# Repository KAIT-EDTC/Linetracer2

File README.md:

# Linetracer2 — 子ども向け教材ライントレーサー

Raspberry Pi Pico ＋ TC78H653FTG ＋ 130 モーター ×2 の、**全部足付き部品（スルーホール）で子どもが自分ではんだ付けできる**ライントレーサー。
基板そのものがシャーシで、センサー 6 個を基板の裏に直付けし、3D プリント（Bambu Lab P1S）のギヤボックス（1 段 5:1）で 130 モーターを高速に回す。
**テープ・接着剤は使わず、M3 ねじ（2 種類）と 3D プリントのツメで組み立てる。** 部品は秋月・ホームセンター・タミヤ品など、**T 番号のある店で買える定番品だけ**。

| 基板（表） | 組み立て図 |
|---|---|
|  |  |

| 項目 | 内容 |
|------|------|
| マイコン | Raspberry Pi Pico（Pico 2 / Pico W も可）、MicroPython |
| モータードライバ | 東芝 TC78H653FTG（秋月 AE-TC78H653FTG モジュール ¥200、スモールモード 2A×2ch） |
| モーター・駆動 | FA-130RA-2270 ×2、タミヤ 8T ピニオン → 3D プリント 40T（m0.5）1 段 5:1、車輪 φ32（O リング P-24）、車軸は車輪と一体で印刷（φ3.5） |
| センサー | フォトリフレクタ LBR-123F ×6（TC4051BP で ADC 1 本に切替、外乱光キャンセル付き） |
| 電源 | 単3×3本（アルカリ 4.5V / ニッケル水素 3.6V）。電池ボックスはデッキにねじ止め、スイッチで ON/OFF |
| 基板 | 2 層 100×100 mm、1.6 mm、全部品スルーホール（ピッチ 2.54 mm 以上、センサーのみ 1.8 mm）、**rev.A1** |
| 3D プリント | 枠 L/R・デッキ・平歯車 ×2・車輪 ×2・ツメで差し込むスキッド（PLA 約 30 g、サポート不要）。電池ボックスをツメで留めるデッキも用意（任意） |
| UI | ボタン×2（START/SELECT）、LED×3、圧電ブザー（オプション）、I2C 拡張（OLED を直挿し可） |
| 性能（計算値） | 最高速度 理論 5 m/s（ソフトで 1.5〜2.5 m/s に制限）、加速 4 m/s² でモーター電流 約 1.4 A |
| コスト（1 台） | 全部新品 約 ¥2,370、**Pico を再利用すれば 約 ¥1,500**（`docs/05_bom.md`） |

## 「Linetracer2 Lite」（rev.L4：XIAO ESP32C6（ピンヘッダ）＋ LBR-127HLD ＋ ブザー ＋ フルカラー LED ＋ 5 V 昇降圧）

標準版から部品を減らした版も用意した（詳しくは [lite/README.md](lite/README.md)）。**Lite のファイルはすべて `lite/` フォルダにまとめてあり、標準版のファイルとは混ざらない**。**枠・デッキ・平歯車・車輪の 3D プリント部品、ねじ、モーター、電池ボックスは標準版と共通**で、基板・ソフト・前の支え（Lite 用ボールキャスター）が違う。
rev.L2（2026-10-05）でマイコンを **Seeed Studio XIAO ESP32C6**、センサーを **LBR-127HLD** に変え、rev.L3（2026-10-07）で **XIAO をピンヘッダ付けに、ブザーとフルカラー LED 6 こ・テストパッドを追加、配線を全部手で引き直し（交差なし・ビア 0）、Lite 用ボールキャスター**を作った。ロボット全体の 3D モデル（STL / GLB）もある。
**rev.L4（2026-10-30）**: モーターに力がかかる（車輪を止める・100 % で走り出す）と電池が 2.5〜3.3 V まで下がって XIAO がリセットしていたので、**XIAO の電源を昇降圧モジュール（秋月 AE-TPS63802、5 V）で作る**ようにし、ほかの回路の問題（USB の VBUS に 470 µF、フルカラー LED の信号の電圧、ニッケル水素で動かない など）も直した（[lite/README.md](lite/README.md) §0）。**KiCad のファイル・Gerber はまだ rev.L3 のまま**（生成スクリプトは rev.L4。KiCad 10 で作り直してから発注）。

| | 標準版 rev.A1 | Lite rev.L4 |
|---|---|---|
| マイコン | Pico をピンヘッダで付ける | **XIAO ESP32C6 をピンヘッダで付ける**（Wi-Fi / Bluetooth 付き） |
| センサー | LBR-123F 6 個 ＋ マルチプレクサ TC4051BP | **LBR-127HLD 3 個を ADC に直結**（マルチプレクサなし） |
| ボタン / LED / ブザー | 2 / 3 / オプション | **1 / フルカラー 6（PL9823、左右に 3 こずつ、信号線 1 本）/ あり（START ボタンと同じピン）**（XIAO の黄 LED も使える） |
| タイヤ / 前の支え | O リング P-24 / スキッド 4.0 mm | **TPU の印刷タイヤ / ボールキャスター 7.5 mm**（センサーが背高なので前を上げる） |
| マイコンの電源 | 電池 → ダイオード → Pico の VSYS（Pico の中は昇降圧） | **電池 → 昇降圧モジュール AE-TPS63802（5 V）→ ダイオード → XIAO の 5V ピン**（rev.L4。モーターで電池が下がっても XIAO が止まらない） |
| 電池電圧の測定 | あり | **なし**（XIAO の ADC 3 本をセンサーで使い切る） |
| はんだ付け | 約 230 か所 | **約 146 か所** |
| 基板 / シルク | 100 × 100 mm / 英語中心 | **65 × 100 mm** / **記号だけ**（つくる順番 ①〜⑰・＋−・抵抗の色）。説明は手順書 `lite/docs/assembly.md` |
| **1 台の部品代（全部新品）** | 約 ¥2,370 | **約 ¥3,530（+¥1,160。うち 5 V 昇降圧モジュール ¥780）** |

> Lite rev.L3 / L4 はマイコンをピンヘッダで付ける。基板側を**ピンソケット**にすれば、標準版のようにマイコンを回収して使い回すこともできる（`lite/docs/assembly.md` §3）。

| Lite のロボット全体（3D） | Lite の基板（3D） |
|---|---|
|  |  |

## ドキュメント

| ファイル | 内容 |
|---------|------|
| [docs/01_requirements.md](docs/01_requirements.md) | 要件定義（依頼内容・派生要件・買い方のルール・コスト目標） |
| [docs/02_concept.md](docs/02_concept.md) | 形・寸法・駆動系の計算・重心・電池 |
| [docs/03_circuit.md](docs/03_circuit.md) | 回路設計（ピン割り当て表、各ブロックの計算） |
| [docs/04_pcb.md](docs/04_pcb.md) | 基板設計（改訂履歴・配置・配線・DRC・発注方法・再生成方法） |
| [docs/05_bom.md](docs/05_bom.md) | 部品表（秋月の通販コード・買う店）、コスト、10 台分の買い物リスト |
| [docs/06_assembly.md](docs/06_assembly.md) | 組み立て手順書（はんだ付けの順番・チェック・ねじ止め・トラブル） |
| [docs/07_firmware.md](docs/07_firmware.md) | ソフトウェア（MicroPython のセットアップ、ライブラリ、PD 制御の調整） |
| [docs/08_knowledge.md](docs/08_knowledge.md) | 知見メモ（部品のクセ、買い方、KiCad/Freerouting/OpenSCAD のハマりどころ、設計判断） |
| [lite/README.md](lite/README.md) | **Lite rev.L4**（**§0: XIAO が落ちる原因と電源の作り直し**、XIAO ESP32C6 ＋ LBR-127HLD ＋ ブザー。変更点と理由、配線のルール、コスト比較、回路・基板・部品表・組み立て・ソフトの違い） |
| [lite/docs/assembly.md](lite/docs/assembly.md) | Lite の組み立て手順書（基板の記号の見かた、つくる順番 ①〜⑰） |
| [lite/hardware/Linetracer2-Lite_assembly.stl](lite/hardware/Linetracer2-Lite_assembly.stl) | **Lite のロボット全体の 3D**（基板・部品・枠・モーター・ギヤ・電池ボックス・キャスター。STL、ブラウザで回して見られる。色つきは同じ名前の `.glb`） |
| [hardware/mechanical/README.md](hardware/mechanical/README.md) | 3D プリント部品と P1S の印刷設定、ねじの一覧 |
| [hardware/mechanical/assembly.stl](hardware/mechanical/assembly.stl) | 全体を組み立てた 3D（STL、ブラウザで回して見られる） |
| [hardware/kicad/Linetracer2_pcb.step](hardware/kicad/Linetracer2_pcb.step) | 部品付き基板の 3D（STEP、Fusion 等の CAD 用） |
| [docs/Linetracer2_schematic.pdf](docs/Linetracer2_schematic.pdf) | 回路図 PDF |
| [lite/docs/Linetracer2-Lite_schematic.pdf](lite/docs/Linetracer2-Lite_schematic.pdf) | Lite の回路図 PDF |
| [docs/datasheets/README.md](docs/datasheets/README.md) | 使った部品のデータシート（リンク集） |

## フォルダ構成

```
Linetracer2/
├── README.md
├── docs/                     設計資料（Markdown）、回路図/基板 PDF、画像、データシートのリンク
├── hardware/
│   ├── kicad/                KiCad 10 プロジェクト（.kicad_pro / _sch / _pcb）
│   │   ├── lib/              自作シンボル・フットプリント（TC78H653 モジュール、LBR-123F、ブザー等）
│   │   ├── bom/              部品表 CSV（秋月の通販コード入り）
│   │   └── reports/          ERC / DRC レポート、ネットリスト
│   ├── gerber/               製造用 Gerber・ドリル
│   ├── Linetracer2_rev.A1_gerber.zip   ← 基板メーカーにそのまま渡す
│   └── mechanical/           3D プリント部品（OpenSCAD 元データ、STL、組み立て図。両方の版で共通。Lite は前の支えだけ 7.5 mm）
├── firmware/micropython/     ライブラリ・標準プログラム・授業用サンプル
├── scripts/                  回路図・基板を生成するスクリプト（再生成用。LT2_VARIANT=lite で Lite も作る）
└── lite/                     ★ Lite 一式（rev.L4: XIAO ESP32C6 版。標準版とは別フォルダ）
    ├── README.md             Lite の設計書（変更点・コスト比較・組み立て・ソフト）
    ├── docs/                 回路図/組立図 PDF、3D 画像
    ├── hardware/             KiCad プロジェクト、Gerber（Linetracer2-Lite_rev.L3_gerber.zip）、ロボット全体の 3D（STL / GLB）
    ├── firmware/micropython/ Lite 用ソフト（XIAO ESP32C6 用 MicroPython。センサー 3 個・ボタン 1 個・フルカラー LED 6 個・ブザー）
    └── scripts/              Lite 専用の生成スクリプト（回路図・配置と手で引いた配線・シルク・配置の確認用の絵）
```

## 状態（2026-10-05, rev.A1）

- [x] 要件定義・構成・駆動系の計算
- [x] 回路図（ERC エラー 0・警告 0）
- [x] 基板レイアウト・配線（DRC エラー 0、未配線 0）、Gerber 出力（rev.A1: ブザーの穴を追加）
- [x] 部品選定・BOM・コスト見積り（T 番号のある店・定番品だけ）
- [x] 3D プリント部品（ねじ止めのデッキ、印刷できる 40T 平歯車、干渉チェック済み）
- [x] MicroPython ライブラリとサンプル
- [ ] **試作 1 台目の製作と実測**（センサーの感度、ギヤのかみ合い、PD ゲイン、電池の持ち）
- [ ] 試作結果を反映した rev.B（`docs/04_pcb.md` §7）
- [x] 低コスト版 Lite rev.L1 の回路図・基板（ERC 0・DRC 0・警告 0）・部品表・ソフト（2026-10-05）
- [x] Lite rev.L2（XIAO ESP32C6 ＋ LBR-127HLD）の回路図・基板・部品表・ソフト・スキッド 7.5 mm（2026-10-05）
- [x] Lite rev.L3（XIAO をピンヘッダで、ブザー、手で引いた配線、Lite 用ボールキャスター、ロボット全体の 3D と干渉チェック）（2026-10-07）
- [x] Lite rev.L4 の回路・配置と配線（生成スクリプト）: XIAO 用 5 V 昇降圧、USB と電源の分け方、フルカラー LED の信号の電圧（2026-10-30）
- [ ] Lite rev.L4 を KiCad 10 で作り直す（回路図・基板・DRC・Gerber・絵・3D、`lite/README.md` §0.6・§9）
- [ ] Lite の試作（LBR-127HLD の高さ、キャスターの転がり、3 センサーでの走り、`lite/README.md` §10）

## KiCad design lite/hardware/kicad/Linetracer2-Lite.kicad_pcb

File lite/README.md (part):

# Linetracer2 Lite（rev.L4：XIAO ESP32C6（ピンヘッダ）＋ LBR-127HLD ＋ ブザー ＋ フルカラー LED ＋ 5 V 昇降圧）

> 最終更新: 2026-10-30（**rev.L4**: モーターに力がかかると XIAO が落ちる問題を、マイコンの電源を作り直して直した（§0）。**未製造・未試作**）
> **注意: KiCad のファイル（回路図・基板・Gerber・PDF・絵・3D）はまだ rev.L3 のまま**。rev.L4 は生成スクリプトに入っている。§9 のコマンドで作り直し、DRC を通してから発注する。**今の Gerber（rev.L3）は発注しない**（§0.6）。
> 標準版（rev.A1）から部品を減らした版。マイコンは **Seeed Studio XIAO ESP32C6**、センサーは **LBR-127HLD**。rev.L3 で **XIAO をピンヘッダで付ける**ようにし、**ブザー**と**フルカラー LED 6 こ**、**テストパッド**を足し、**配線を全部手で引き直して**（自動配線をやめた）、**Lite 用のボールキャスター**を作った（§1）。
> **枠・デッキ・平歯車・車輪の 3D プリント部品、ねじ、モーター、電池ボックス、枠のねじ穴は標準版と共通**。違うのは基板（外形と中身）・ソフト・**前の支え（高さ 7.5 mm のボールキャスターかスキッド）**。
> **Lite のファイルはすべてこの `lite/` フォルダの中**（下のパスは `lite/` からの相対パス）。標準版のファイル（リポジトリ直下の `hardware/` `docs/` `firmware/`）とは混ざらない。
> 回路図: `hardware/kicad/Linetracer2-Lite.kicad_sch`（PDF: `docs/Linetracer2-Lite_schematic.pdf`）
> 製造データ: `hardware/Linetracer2-Lite_rev.L3_gerber.zip`（**rev.L3、XIAO が落ちる問題あり**。rev.L4 は KiCad で作り直すと `Linetracer2-Lite_rev.L4_gerber.zip`）　ソフト: `firmware/micropython/`（Arduino C++ 版: [`firmware/arduino/`](firmware/arduino/README.md)）　組み立て手順書: [`docs/assembly.md`](docs/assembly.md)
> **ロボット全体の 3D モデル**: `hardware/Linetracer2-Lite_assembly.stl`（GitHub 上でそのまま回して見られる）、色つき `hardware/Linetracer2-Lite_assembly.glb`。部品付き基板だけの STEP: `hardware/kicad/Linetracer2-Lite_pcb.step`
> 前の版 rev.L2（XIAO じか付け、自動配線）は git の履歴とプルリクエスト #3 に、rev.L1（Pico ＋ LBR-123F）はコミット `1db5a53` に残っている。

| ロボット全体（3D） | 横から |
|---|---|
|  |  |

| 基板の上面（3D） | 裏面（3D、センサー面） |
|---|---|
|  |  |

| シルク（表。子どもが読む印刷） | シルク（裏、下から見た向き） |
|---|---|
|  |  |

---

## 0. rev.L4（2026-10-30）: モーターに力がかかると XIAO が落ちる → 電源を作り直した

依頼「モーターにトルクをかけたときや、モーター出力 100 % にしたときに XIAO が落ちるので回路を組み直して。ほかにも回路的に良くないところ・問題点をくまなく見て」への答え。

### 0.1 原因: XIAO の電源が、モーターと同じ電池から「ダイオード 1 本」でとっていた

rev.L3 は `単3×3 ─ D1 ─ XIAO の 5V ピン` だった。XIAO の中は `5V ピン ─ ショットキー（約 0.3 V）─ 降圧 DC-DC ─ 3.3 V` なので、3.3 V を保つには電池の側で**約 4.0 V**、ESP32-C6 がリセットしないためにも**約 3.4 V** 要る。ところが単3 アルカリ 3 本は、モーターが大きい電流を流すとすぐその下まで下がる。

計算の前提: 電池 3 本 ＋ 電池ボックスのばね・スイッチ・線の抵抗 ≒ 0.7 Ω（新品）、FA-130RA-2270 の巻線 ≒ 0.68 Ω（1.5 V で止めると 2.2 A）、TC78H653FTG（スモールモード）のオン抵抗 0.22 Ω、ソフトの 100 % = 電池の 71 %（3.0 V ÷ 4.2 V）。

| 場面 | 電池から出る電流 | 電池の電圧（新品 4.65 V） | rev.L3 の XIAO |
|---|---|---|---|
| ふつうに走っている（2 つで 1 A くらい） | 約 1.0 A | 約 3.9 V | ぎりぎり動く |
| **片方の車輪を手で止めて 100 %**（もう片方は止まっている） | 約 1.9 A | **約 3.3 V** | **リセット** |
| **2 つとも 100 % で走り出す・2 つとも止める** | 約 2.9 A | **約 2.6 V** | **リセット** |
| （少し減った電池 3.9 V・1.2 Ω で 2 つとも止める） | 約 1.9 A | 約 1.7 V | リセット |

- 470 µF（C2）は 0.2 A で 1 ms ほどしか持たない。モーターが止まっている間（何百 ms）は支えられない。
- つまり**ソフトの問題ではなく、電源の作り方の問題**。走り出しのソフトスタート（`RAMP_PER_CALL`）は入っているが、車輪を止められると電流は減らない。
- 標準版（Pico）では起きにくい: Pico の VSYS の中に**昇降圧の DC-DC（1.8〜5.5 V）**があるから。XIAO ESP32C6 の中は降圧だけなので、Lite では外に昇降圧が要る。

### 0.2 なおしかた: XIAO 専用の 5 V を、昇降圧モジュールで作る

```
単3×3 ─ VBAT ─┬─ モータードライバ VM（C1 470µF）
              └─ D1 1N5819 ─ VIN_BB ─ U3 AE-TPS63802（昇降圧、VR1 = 470kΩ → 5.13 V、EN = VIN）
                                        └─ VOUT_BB ─ D8 1N5819 ─ VSYS（約 4.8 V）─┬─ XIAO 5V ピン → 3.3 V
                                                                                   ├─ 右のフルカラー LED 3 こ（D5〜D7）
                                                                                   └─ D9 1N4148 ─ VLED_L（約 4.1 V）─ 左の 3 こ（D2〜D4）
              USB-C の 5 V も VSYS に来る（XIAO の中で直結）。D8 があるので U3 には流れない
```

- **U3 = 秋月 AE-TPS63802**（TI TPS63802 の昇降圧モジュールキット、¥780、20 × 13 mm、4 ピン: VIN・GND・VOUT・EN）。**入力 1.3〜5.5 V で動き続け**（はじめの起動は 1.8 V 以上）、スイッチ電流 2 A。電池が**約 1.6 V**（D1 のあとで 1.3 V）まで下がっても XIAO に 5 V を出す。上の表のいちばん悪い場面（2.6 V）でも余裕がある。
  - 昇圧だけでなく**昇降圧**なので、新品のアルカリ（4.8 V）でもニッケル水素（3.6 V）でも同じ 5.13 V。
  - 秋月で買えて、ピンヘッダで付けられて、1 A 近く出せるのはこれだけだった。もっと安い昇圧モジュール（AE-XCL102 / XCL103、5 V）は出力 0.2 A ほどで、Wi-Fi（`03_WiFiControl`）やフルカラー LED を使うと足りない。
  - 出力は VR1（25 回転の半固定抵抗）で決まる。**VR1 の代わりに 470 kΩ の抵抗を付けて 5.13 V に固定**（秋月の説明書の表の値。半固定抵抗だと回してしまう・高さがある）。**VR1 が空のまま電気を入れるとこわれる**ので、先生が先に付けて単3 ×2 本でためす（手順書 §0）。
  - EN は VIN につないで「いつも ON」（TI の注意: EN を浮かせてはいけない）。モードのジャンパーはそのまま（強制 PWM）。
- **D8**（1N5819）: XIAO の 5V ピンは USB の VBUS と直結。D8 が無いと、U3 が PC の USB に電気を押しこみ、USB の 5 V が U3 の出力に逆から入る。D8 のおかげで VSYS は約 4.8 V（USB の 5 V より少し低い）: **USB をつなぐと USB から、外すとすぐ U3 から**。
- **D1**（1N5819）はそのまま: 電池を逆につないだとき、U3 と XIAO を守る（U3 の入力は −0.3 V まで）。
- **C2（VSYS の 470 µF）はやめた**: VSYS は USB の VBUS そのもので、USB の決まりは 10 µF まで（差した瞬間の突入電流で PC のポートが落ちることがある）。U3 の出力にはモジュールのコンデンサがある。
- XIAO の 5V ピンには約 4.8 V。中の降圧 DC-DC にとって十分（3.6 V 以上あればよい）。

### 0.3 ほかに見つけた回路の問題と対応

| # | 問題 | どうなるか | rev.L4 |
|---|---|---|---|
| 1 | **XIAO の電源が電池じか**（§0.1） | モーターに力がかかると XIAO がリセット | **U3（5 V 昇降圧）を足した** |
| 2 | **ニッケル水素 3 本（3.6 V）だと、止まっていても足りない**（rev.L3 の説明は「NiMH は `BATTERY_VOLT` を 3.7 に」としていたが、XIAO の 3.3 V が保てない） | 不安定・動かない | U3 で解決（NiMH でも 5.13 V。内部抵抗が小さいのでモーターにはむしろよい） |
| 3 | **USB の VBUS（= VSYS）に 470 µF（C2）** | USB を差した瞬間の突入電流（規格は 10 µF まで）。PC のポートが落ちる・つながらないことがある | C2 をやめた（部品が 1 つ減った） |
| 4 | **フルカラー LED の信号の電圧が足りない**: PL9823 は VDD の 0.7 倍より高いと「1」。USB の 5 V では 3.5 V 要るが、XIAO は 3.3 V | USB だけだと光らない・色がおかしい（rev.L3 §10 で心配していたこと）。U3 で VSYS が 4.8 V に上がると電池でも同じになる | **左の 3 こ（信号が最初に入る D2 を含む）の電源を D9（1N4148）で 0.7 V 下げた**: 約 4.1 V → 2.9 V で「1」。D2〜D4 は自分の VDD（4.1 V）で次へ信号を渡すので、右の 3 こ（4.8 V → 3.4 V）にも足りる |
| 5 | フルカラー LED の電源が電池 − D1（新品で約 4.2 V）で、決まり（4.5〜6 V）より低い | 電池が減ると青と緑が暗くなる | 右の 3 こは 4.8 V（決まりの中）。左の 3 こは 4.1 V（rev.L3 と同じくらい、でも電池が減っても変わらない） |
| 6 | 電池の電圧を測れない（ADC のピンが 3 本しかなく、センサーで使っている） | 電池が減ったのが分からない | 変わらず。rev.L4 ではリセットしなくなる代わりに、だんだん遅くなる。ほぼ空（約 1.6 V）で U3 が止まる → XIAO がリセット（「ド・ミ・ソ」がまた鳴る）が電池交換のサイン |
| 7 | 電池の ＋ − が逆（J1 を逆にはんだ付けしたとき） | モータードライバの中のダイオードで電池がショートする（ドライバがこわれ、電池・線が熱くなる） | 変わらず（D1 が U3 と XIAO は守る）。ショート対策のリセッタブルヒューズ（PTC）は、0.1 Ω ほどの抵抗でモーターの電圧をさらに下げ、モーターを止めたときの電流で切れてしまうので見送り。手順書 ⑩ ★ の向きの確認で防ぐ |
| 8 | 車輪を止めたまま 100 % を続けると、ドライバの過電流保護（ISD）が働き、ソフトが 0.1 秒ごとに戻す | 大きい電流がくり返し流れ、モーターが熱くなる | rev.L3 では XIAO がリセットして（たまたま）止まっていた。rev.L4 では止まらないので、**車輪を手で止めつづけない**（電流を測るピンがないのでソフトでは見分けられない） |
| 9 | フルカラー LED にパスコン（0.1 µF）がない | ちらつくかもしれない | 変わらず。VSYS は U3 の出力で安定するようになった。ちらつくなら次の版で足す（§10） |
| 10 | XIAO の 5V ピンは USB と直結 → 外の電源は必ずダイオード経由 | ― | rev.L3（D1）と同じ考えで D8 |

ソフトの変更はない（ピンは rev.L3 と同じ）。`linetracer.py`・Arduino 版のコメントと、`08_test_pads.py` の VSYS の目安だけ直した。

### 0.4 配置と配線（rev.L4）

（`scripts/preview_layout.py` の絵。赤 = 表、青 = 裏。KiCad で作った絵ではない）

- **U3 は真ん中**（ブザーと XIAO のアンテナの間）に、自分のピンヘッダでねかせる（2.5 mm 浮く）。下は線だけ（3 本のバスなど）。XIAO のアンテナの禁止エリアから 2 mm、IN2 の線から 0.4 mm。
- **D1・D8 は U3 の左にたてに 2 本**。D9 は前の R7 と R1 の間（裏の横の線（VSYS）を D9 で 2 つに分けた）。
- **電池（U3 の入力）と 5 V（VSYS）は、モータードライバのモジュールの下**（2 列のピンの間。モジュールは 2.5 mm 浮いている）を 2 本の線で通した。右うしろ（ドライバの VM のピン、XIAO の 5V ピン）から真ん中へ、XIAO のアンテナの禁止エリアと STBY の線（裏）をよけて、**交差なしで行ける道はここだけ**。線の太さは 0.6 mm（1 A まで）、ビア 0 のまま。
- C2・前の D1 の場所（右うしろ）があいたので、ロボットの名前をそこへ。テストパッド GND（TP1）はスタートボタンのうしろへ（前の場所は U3 の下になる）。**抵抗の絵は U3 の四角の中**（抵抗は ①〜③、U3 は ⑬ なので、使うときには見える）。
- つくる順番を **①〜⑰** に付け直した: ④ 1N5819 ×2（D1・D8）→ ⑤ 1N4148（D9）→ ⑥ 0.1 µF → ⑦ トランジスタ → ⑧ ボタン → ⑨ ブザー → ⑩ でんち → ⑪ ドライバー → ⑫ XIAO → **⑬ でんげん（U3）** → ⑭ フルカラー LED → ⑮ 470 µF（C1 だけ）→ ⑯ センサー（裏）→ ⑰ モーター。
- 確かめたこと: 線は縦・横・45° だけ（`check_angles()`）。KiCad の DRC の代わりに、配置・配線のデータから**すき間 0.2 mm 以上と、全部のネットがつながっていること**を調べる簡単なチェックを作って、**エラー 0**（同じチェックで rev.L3 も 0、わざと近づけると検出する）。**KiCad の DRC・回路図との照合はまだ**（§0.6）。
- **U3 の外形は推定**: 秋月の資料の寸法（20 / 13 / 1.8 / 2.7 / 2.54 mm）から「4 本のピンが 13 mm の辺に、端から 1.8 mm」とした。モジュールは**裏返してもピンは同じ穴のまま、体が列の反対側に来る**ので、四角に入る向きで付けられる（部品の面を下にするときは VR1 の 470 kΩ をねかせて 2.5 mm 以下）。**発注の前に実物か秋月の外形図で確かめる**（§10）。

### 0.5 部品とコスト（1 台）

| | 変化 |
|---|---|
| U3 昇降圧モジュール AE-TPS63802（秋月 115557、4 ピンのピンヘッダ付き） | +¥780 |
| VR1 の代わりの抵抗 470 kΩ（125474） | +¥1 |
| D8 1N5819（D1 と同じ） | +¥10 |
| D9 1N4148 | +≒¥2 |
| C2 470 µF をやめた | −¥10 |
| **合計** | **+≒¥783 → 1 台 約 ¥3,530**（rev.L3 約 ¥2,745） |

はんだ付けは子どもが +6 か所（U3 の 4、D8・D9、C2 −2）、先生が U3 の準備で 6 か所（ピンヘッダ 4、470 kΩ 2）。

### 0.6 このとき作ったもの・まだのもの

| | 状態 |
|---|---|
| 回路図の生成 `scripts/gen_schematic_lite.py` | **rev.L4**（このスクリプトの出力を読む簡単なネットリスタで、ネットが意図どおりか確かめた） |
| シンボル・フットプリント・3D `../scripts/gen_lib.py`・`gen_3d.py` | **rev.L4**（`AE-TPS63802` を追加） |
| 配置と配線 `scripts/layout_lite.py`、シルク `scripts/post_pcb_lite.py`、手順の絵 `scripts/step_images.py` | **rev.L4** |
| ソフト（MicroPython / Arduino） | コメントと目安だけ（ピンは同じ） |
| この README、手順書 `docs/assembly.md`、部品表 `docs/bom.md` | **rev.L4** |
| `hardware/kicad/*.kicad_sch` / `*.kicad_pcb` / ライブラリ、Gerber、BOM の csv、PDF、`docs/*.png`、STEP、ロボット全体の 3D、手順の絵 `docs/steps/` | **まだ rev.L3**。このセッションでは KiCad 10 を入れられなかった（配布元につながらず、ソースからのビルドは止められた）。§9 のコマンドを順に実行すれば全部 rev.L4 になる |

KiCad で作り直したら確かめること: ERC / DRC がエラー 0・警告 0・未接続 0・回路図との不一致 0、シルクが U3 の四角・抵抗の絵・番号で重なっていないか、`export_assembly.sh` の干渉チェックで U3 が何にも当たらないか（U3 は高さ約 6 mm、上には何もない）。

---

## 1. 依頼内容と結論（rev.L3）

2026-10-06 の依頼（4 回目）と、その結果:

| # | 依頼 | 結果 |
|---|------|------|
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
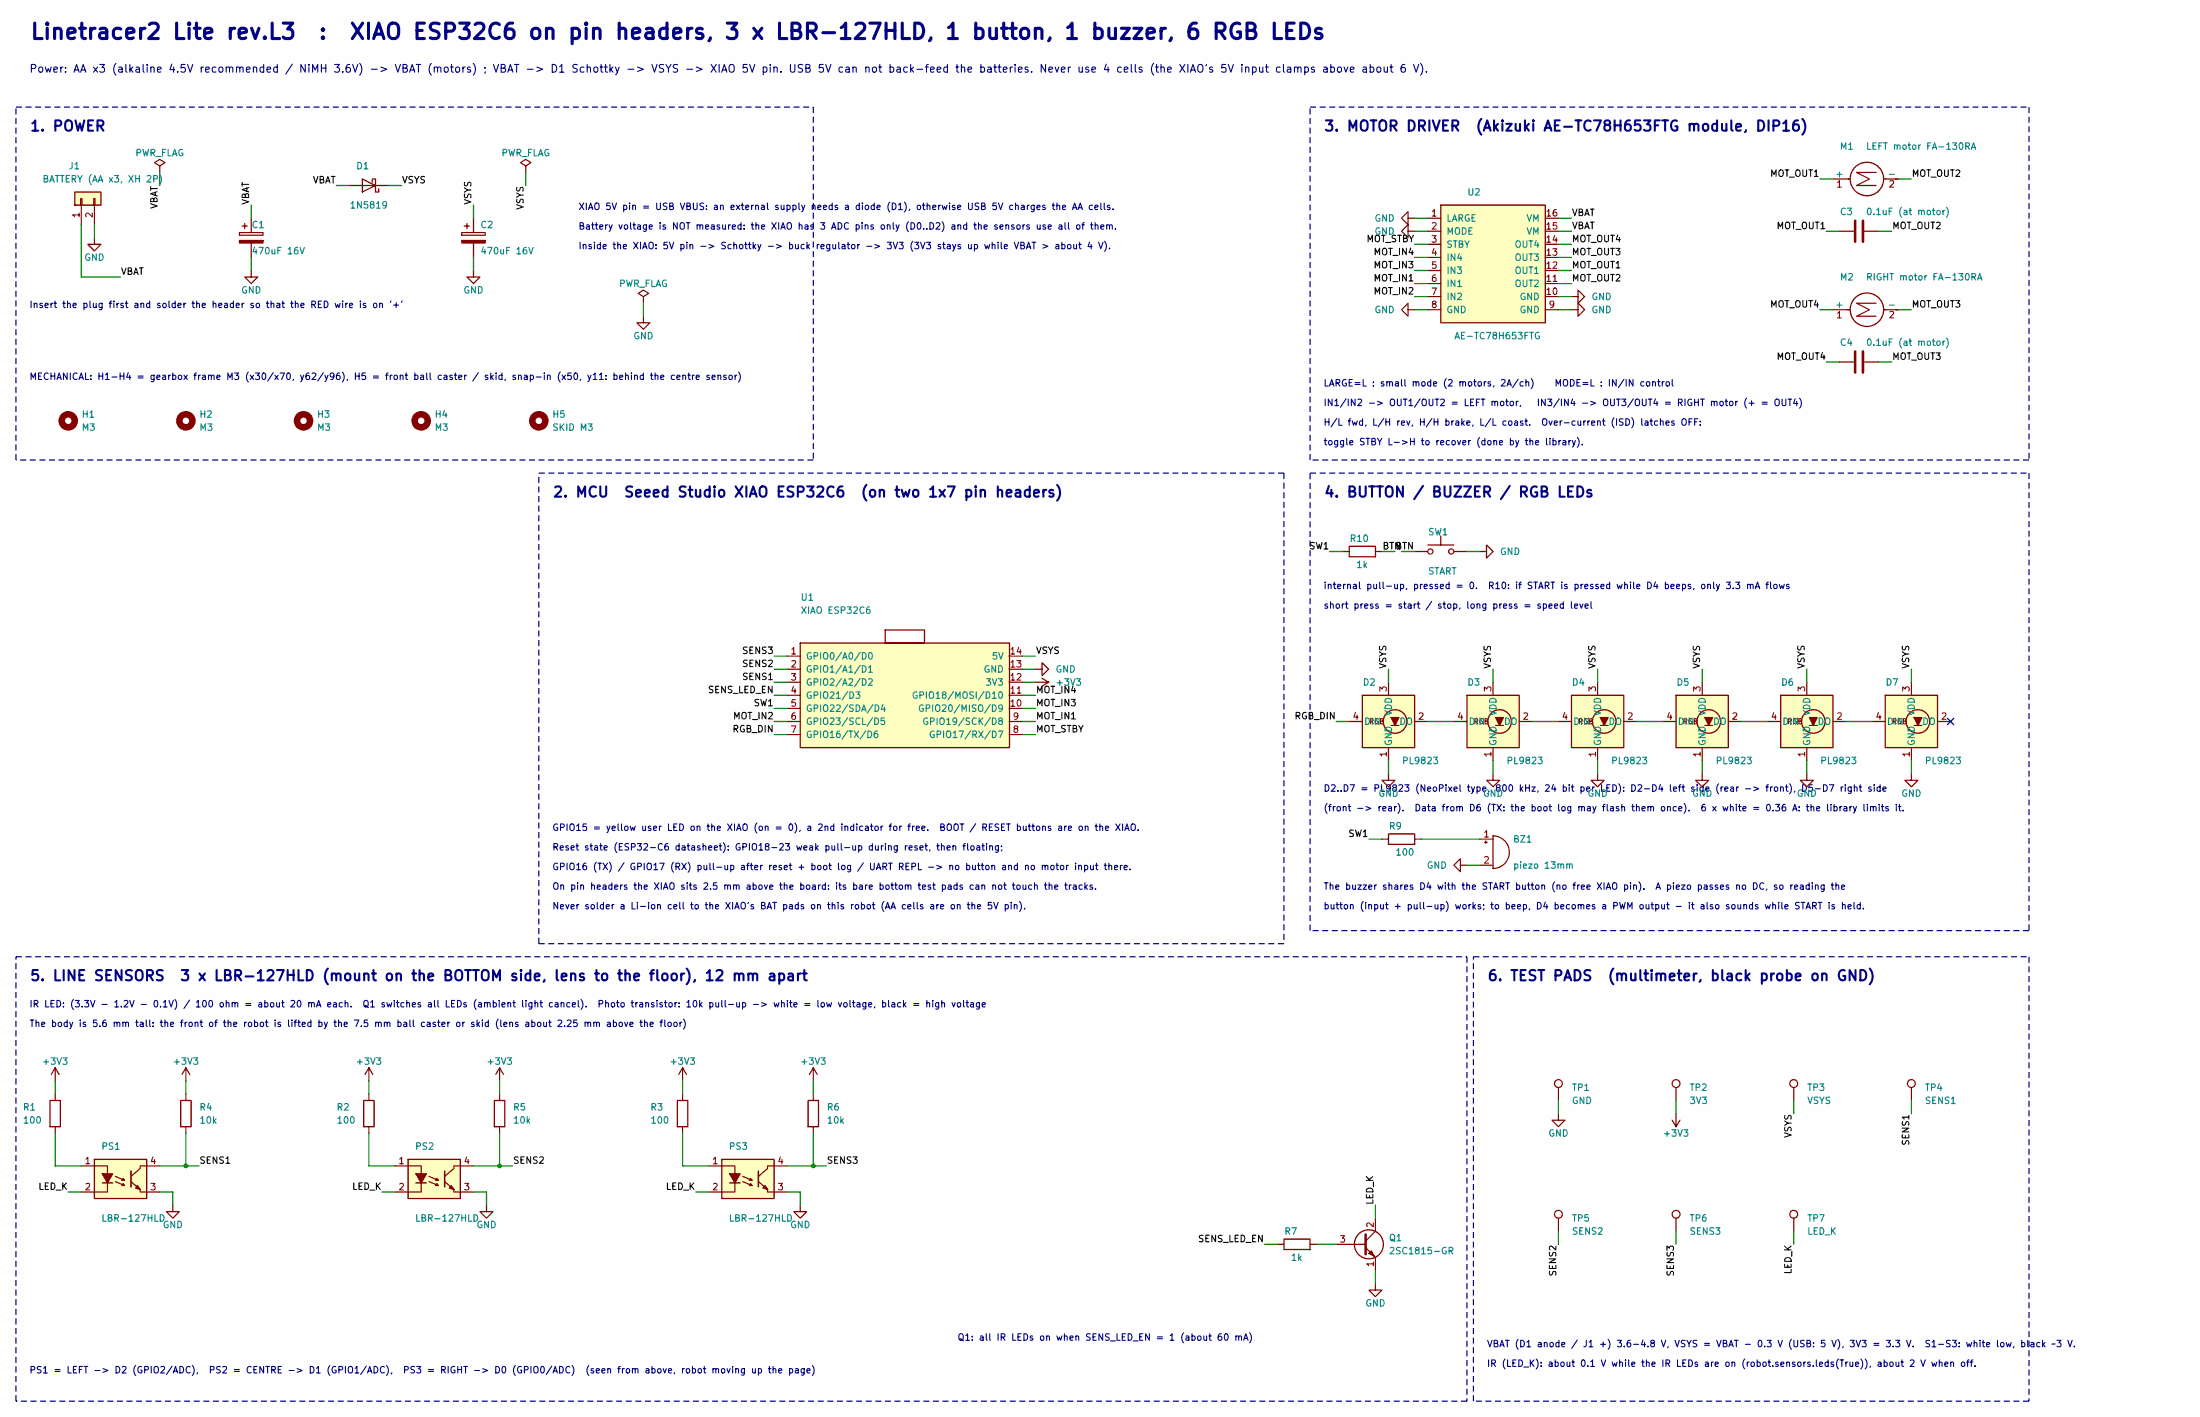
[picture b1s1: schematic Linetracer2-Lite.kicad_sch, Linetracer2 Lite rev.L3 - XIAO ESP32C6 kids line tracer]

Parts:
BZ1: piezo 13mm; Buzzer_PKM13_P5.0
C1, C2: 470uF 16V; CP_Radial_D8.0mm_P3.50mm
C3, C4: 0.1uF (at motor); C_Disc_D3.0mm_W2.0mm_P2.50mm
D1: 1N5819; D_DO-41_SOD81_P10.16mm_Horizontal
D2, D3, D4, D5, D6, D7: PL9823; LED_PL9823_5mm
H1, H2, H3, H4: M3; MountingHole_3.2mm_M3
H5: SKID M3; MountingHole_3.2mm_M3
J1: BATTERY (AA x3, XH 2P); BatteryXH_2P
M1: LEFT motor FA-130RA; MotorPads_2P_Relief
M2: RIGHT motor FA-130RA; MotorPads_2P_Relief
PS1, PS2, PS3: LBR-127HLD
Q1: 2SC1815-GR; TO-92_Inline_Wide
R1, R2, R3, R9: 100; R_Axial_DIN0207_L6.3mm_D2.5mm_P10.16mm_Horizontal
R4, R5, R6: 10k; R_Axial_DIN0207_L6.3mm_D2.5mm_P10.16mm_Horizontal
R7, R10: 1k; R_Axial_DIN0207_L6.3mm_D2.5mm_P10.16mm_Horizontal
SW1: START; SW_PUSH_6mm
TP1: GND; TestPoint_Pad_D1.5mm
TP2: 3V3; TestPoint_Pad_D1.5mm
TP3: VSYS; TestPoint_Pad_D1.5mm
TP4: SENS1; TestPoint_Pad_D1.5mm
TP5: SENS2; TestPoint_Pad_D1.5mm
TP6: SENS3; TestPoint_Pad_D1.5mm
TP7: LED_K; TestPoint_Pad_D1.5mm
U1: XIAO ESP32C6; XIAO_ESP32C6_Header
U2: AE-TC78H653FTG

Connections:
+3V3: R1.1, R2.1, R3.1, R4.1, R5.1, R6.1, TP2.1, U1.12 (3V3)
/BTN: R10.2, SW1.1
/LED_K: PS1.2 (K), PS2.2 (K), PS3.2 (K), Q1.2 (C), TP7.1
/MOT_IN1: U1.9 (GPIO19/SCK/D8), U2.6 (IN1)
/MOT_IN2: U1.6 (GPIO23/SCL/D5), U2.7 (IN2)
/MOT_IN3: U1.10 (GPIO20/MISO/D9), U2.5 (IN3)
/MOT_IN4: U1.11 (GPIO18/MOSI/D10), U2.4 (IN4)
/MOT_OUT1: C3.1, M1.1 (+), U2.12 (OUT1)
/MOT_OUT2: C3.2, M1.2 (-), U2.11 (OUT2)
/MOT_OUT3: C4.2, M2.2 (-), U2.13 (OUT3)
/MOT_OUT4: C4.1, M2.1 (+), U2.14 (OUT4)
/MOT_STBY: U1.8 (GPIO17/RX/D7), U2.3 (STBY)
/RGB_DIN: D2.4 (DIN), U1.7 (GPIO16/TX/D6)
/SENS1: PS1.4 (C), R4.2, TP4.1, U1.3 (GPIO2/A2/D2)
/SENS2: PS2.4 (C), R5.2, TP5.1, U1.2 (GPIO1/A1/D1)
/SENS3: PS3.4 (C), R6.2, TP6.1, U1.1 (GPIO0/A0/D0)
/SENS_LED_EN: R7.1, U1.4 (GPIO21/D3)
/SW1: R9.1, R10.1, U1.5 (GPIO22/SDA/D4)
/VBAT: C1.1, D1.2 (A), J1.1, U2.15 (VM), U2.16 (VM)
/VSYS: C2.1, D1.1 (K), D2.3 (VDD), D3.3 (VDD), D4.3 (VDD), D5.3 (VDD), D6.3 (VDD), D7.3 (VDD), TP3.1, U1.14 (5V)
GND: BZ1.2 (-), C1.2, C2.2, D2.1 (GND), D3.1 (GND), D4.1 (GND), D5.1 (GND), D6.1 (GND), D7.1 (GND), J1.2, PS1.3 (E), PS2.3 (E), PS3.3 (E), Q1.1 (E), SW1.2, TP1.1, U1.13 (GND), U2.1 (LARGE), U2.2 (MODE), U2.8 (GND), U2.9 (GND), U2.10 (GND)
unnamed: BZ1.1 (+), R9.2
unnamed: D2.2 (DO), D3.4 (DIN)
unnamed: D3.2 (DO), D4.4 (DIN)
unnamed: D4.2 (DO), D5.4 (DIN)
unnamed: D5.2 (DO), D6.4 (DIN)
unnamed: D6.2 (DO), D7.4 (DIN)
unnamed: PS1.1 (A), R1.2
unnamed: PS2.1 (A), R2.2
unnamed: PS3.1 (A), R3.2
unnamed: Q1.3 (B), R7.2

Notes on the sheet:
short press = start / stop, long press = speed level
PS1 = LEFT -> D2 (GPIO2/ADC), PS2 = CENTRE -> D1 (GPIO1/ADC), PS3 = RIGHT -> D0 (GPIO0/ADC) (seen from above, robot moving up the page)
6. TEST PADS (multimeter, black probe on GND)
internal pull-up, pressed = 0. R10: if START is pressed while D4 beeps, only 3.3 mA flows
Inside the XIAO: 5V pin -> Schottky -> buck regulator -> 3V3 (3V3 stays up while VBAT > about 4 V).
GPIO15 = yellow user LED on the XIAO (on = 0), a 2nd indicator for free. BOOT / RESET buttons are on the XIAO.
4. BUTTON / BUZZER / RGB LEDs
IN1/IN2 -> OUT1/OUT2 = LEFT motor, IN3/IN4 -> OUT3/OUT4 = RIGHT motor (+ = OUT4)
Power: AA x3 (alkaline 4.5V recommended / NiMH 3.6V) -> VBAT (motors) ; VBAT -> D1 Schottky -> VSYS -> XIAO 5V pin. USB 5V can not back-feed the batteries. Never use 4 cells (the XIAO's 5V input clamps above about 6 V).
2. MCU Seeed Studio XIAO ESP32C6 (on two 1x7 pin headers)
MECHANICAL: H1-H4 = gearbox frame M3 (x30/x70, y62/y96), H5 = front ball caster / skid, snap-in (x50, y11: behind the centre sensor)
Insert the plug first and solder the header so that the RED wire is on '+'
D2..D7 = PL9823 (NeoPixel type, 800 kHz, 24 bit per LED): D2-D4 left side (rear -> front), D5-D7 right side
3. MOTOR DRIVER (Akizuki AE-TC78H653FTG module, DIP16)
Never solder a Li-ion cell to the XIAO's BAT pads on this robot (AA cells are on the 5V pin).
IR (LED_K): about 0.1 V while the IR LEDs are on (robot.sensors.leds(True)), about 2 V when off.
LARGE=L : small mode (2 motors, 2A/ch) MODE=L : IN/IN control
button (input + pull-up) works; to beep, D4 becomes a PWM output - it also sounds while START is held.
1. POWER
VBAT (D1 anode / J1 +) 3.6-4.8 V, VSYS = VBAT - 0.3 V (USB: 5 V), 3V3 = 3.3 V. S1-S3: white low, black ~3 V.
Battery voltage is NOT measured: the XIAO has 3 ADC pins only (D0..D2) and the sensors use all of them.
IR LED: (3.3V - 1.2V - 0.1V) / 100 ohm = about 20 mA each. Q1 switches all LEDs (ambient light cancel). Photo transistor: 10k pull-up -> white = low voltage, black = high voltage
The buzzer shares D4 with the START button (no free XIAO pin). A piezo passes no DC, so reading the
Q1: all IR LEDs on when SENS_LED_EN = 1 (about 60 mA)
The body is 5.6 mm tall: the front of the robot is lifted by the 7.5 mm ball caster or skid (lens about 2.25 mm above the floor)
Reset state (ESP32-C6 datasheet): GPIO18-23 weak pull-up during reset, then floating;
XIAO 5V pin = USB VBUS: an external supply needs a diode (D1), otherwise USB 5V charges the AA cells.
GPIO16 (TX) / GPIO17 (RX) pull-up after reset + boot log / UART REPL -> no button and no motor input there.
H/L fwd, L/H rev, H/H brake, L/L coast. Over-current (ISD) latches OFF:
5. LINE SENSORS 3 x LBR-127HLD (mount on the BOTTOM side, lens to the floor), 12 mm apart
toggle STBY L->H to recover (done by the library).
On pin headers the XIAO sits 2.5 mm above the board: its bare bottom test pads can not touch the tracks.
Linetracer2 Lite rev.L3 : XIAO ESP32C6 on pin headers, 3 x LBR-127HLD, 1 button, 1 buzzer, 6 RGB LEDs
(front -> rear). Data from D6 (TX: the boot log may flash them once). 6 x white = 0.36 A: the library limits it.

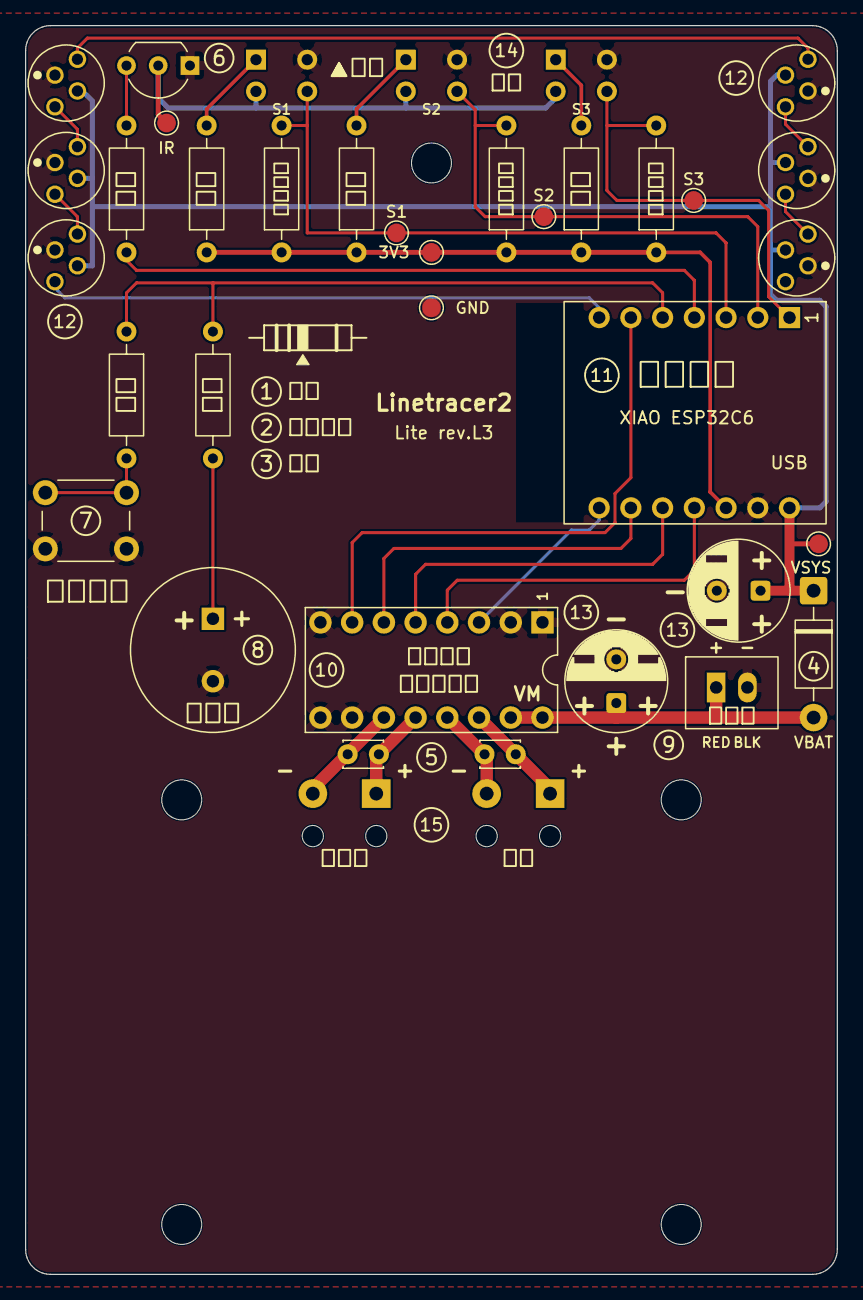
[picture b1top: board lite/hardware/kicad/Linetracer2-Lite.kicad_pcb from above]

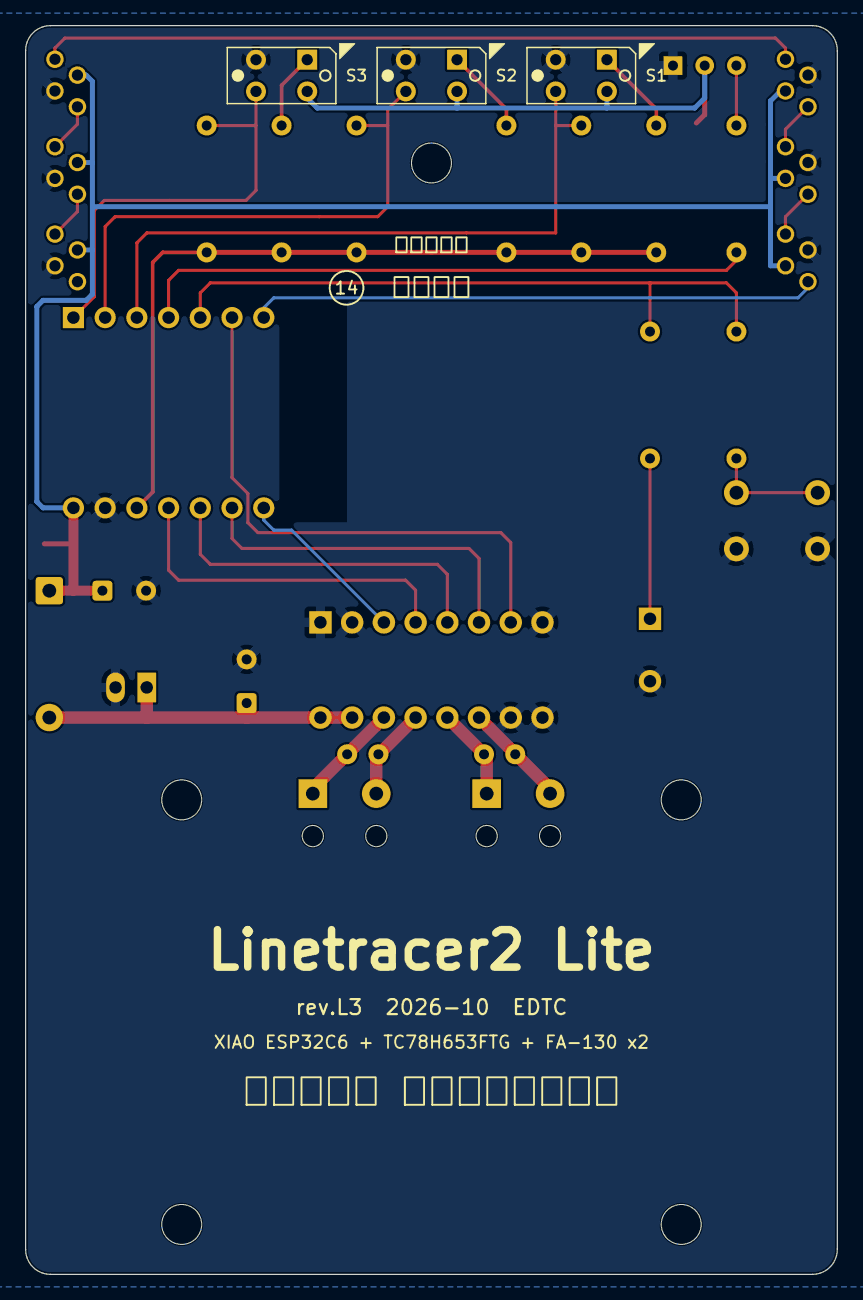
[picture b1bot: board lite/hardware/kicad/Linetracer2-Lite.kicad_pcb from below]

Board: 2 copper layers, 65.0 x 100.0 mm, 43 parts (3 on the bottom side), 31 nets.

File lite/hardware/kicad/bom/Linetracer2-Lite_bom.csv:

"Refs","Value","Footprint","Akizuki","Note","Qty"
"BZ1","piezo 13mm","Linetracer2:Buzzer_PKM13_P5.0","104118 (Murata PKM13EPYH4000-A0)","passive piezo, + on the square pad","1"
"C1,C2","470uF 16V","Capacitor_THT:CP_Radial_D8.0mm_P3.50mm","108426 (Rubycon 16WXA470MEFC 8x9)","hold-up for the XIAO when motors pull the battery down,motor bulk capacitor, place near U2 VM","2"
"C3,C4","0.1uF (at motor)","Capacitor_THT:C_Disc_D3.0mm_W2.0mm_P2.50mm","113582 (10pcs)","","2"
"D1","1N5819","Diode_THT:D_DO-41_SOD81_P10.16mm_Horizontal","117244","blocks USB 5V back-feed into batteries","1"
"D2-D7","PL9823","Linetracer2:LED_PL9823_5mm","108411 (PL9823-F5)","","6"
"J1","BATTERY (AA x3, XH 2P)","Linetracer2:BatteryXH_2P","112247 (B2B-XH-A) / battery box 112243","red wire = + (pin 1)","1"
"M1","LEFT motor  FA-130RA","Linetracer2:MotorPads_2P_Relief","106437","","1"
"M2","RIGHT motor FA-130RA","Linetracer2:MotorPads_2P_Relief","106437","","1"
"PS1-PS3","LBR-127HLD","Linetracer2:LBR-127HLD","104500","","3"
"Q1","2SC1815-GR","Package_TO_SOT_THT:TO-92_Inline_Wide","117089","","1"
"R1-R3,R9","100","Resistor_THT:R_Axial_DIN0207_L6.3mm_D2.5mm_P10.16mm_Horizontal","125101 (100pcs)","","4"
"R4-R6","10k","Resistor_THT:R_Axial_DIN0207_L6.3mm_D2.5mm_P10.16mm_Horizontal","125103 (100pcs)","","3"
"R7,R10","1k","Resistor_THT:R_Axial_DIN0207_L6.3mm_D2.5mm_P10.16mm_Horizontal","125102 (100pcs)","","2"
"SW1","START","Button_Switch_THT:SW_PUSH_6mm","108075","","1"
"U1","XIAO ESP32C6","Linetracer2:XIAO_ESP32C6_Header","129481 (Seeed Studio XIAO ESP32C6) + pin header 1x40 100167 (2 x 7 pins)","solder the XIAO on two 1x7 pin headers (cut from a 1x40 strip), then into the board","1"
"U2","AE-TC78H653FTG","Linetracer2:AE-TC78H653FTG","114746","uses the two 1x8 pin headers that come with the module","1"

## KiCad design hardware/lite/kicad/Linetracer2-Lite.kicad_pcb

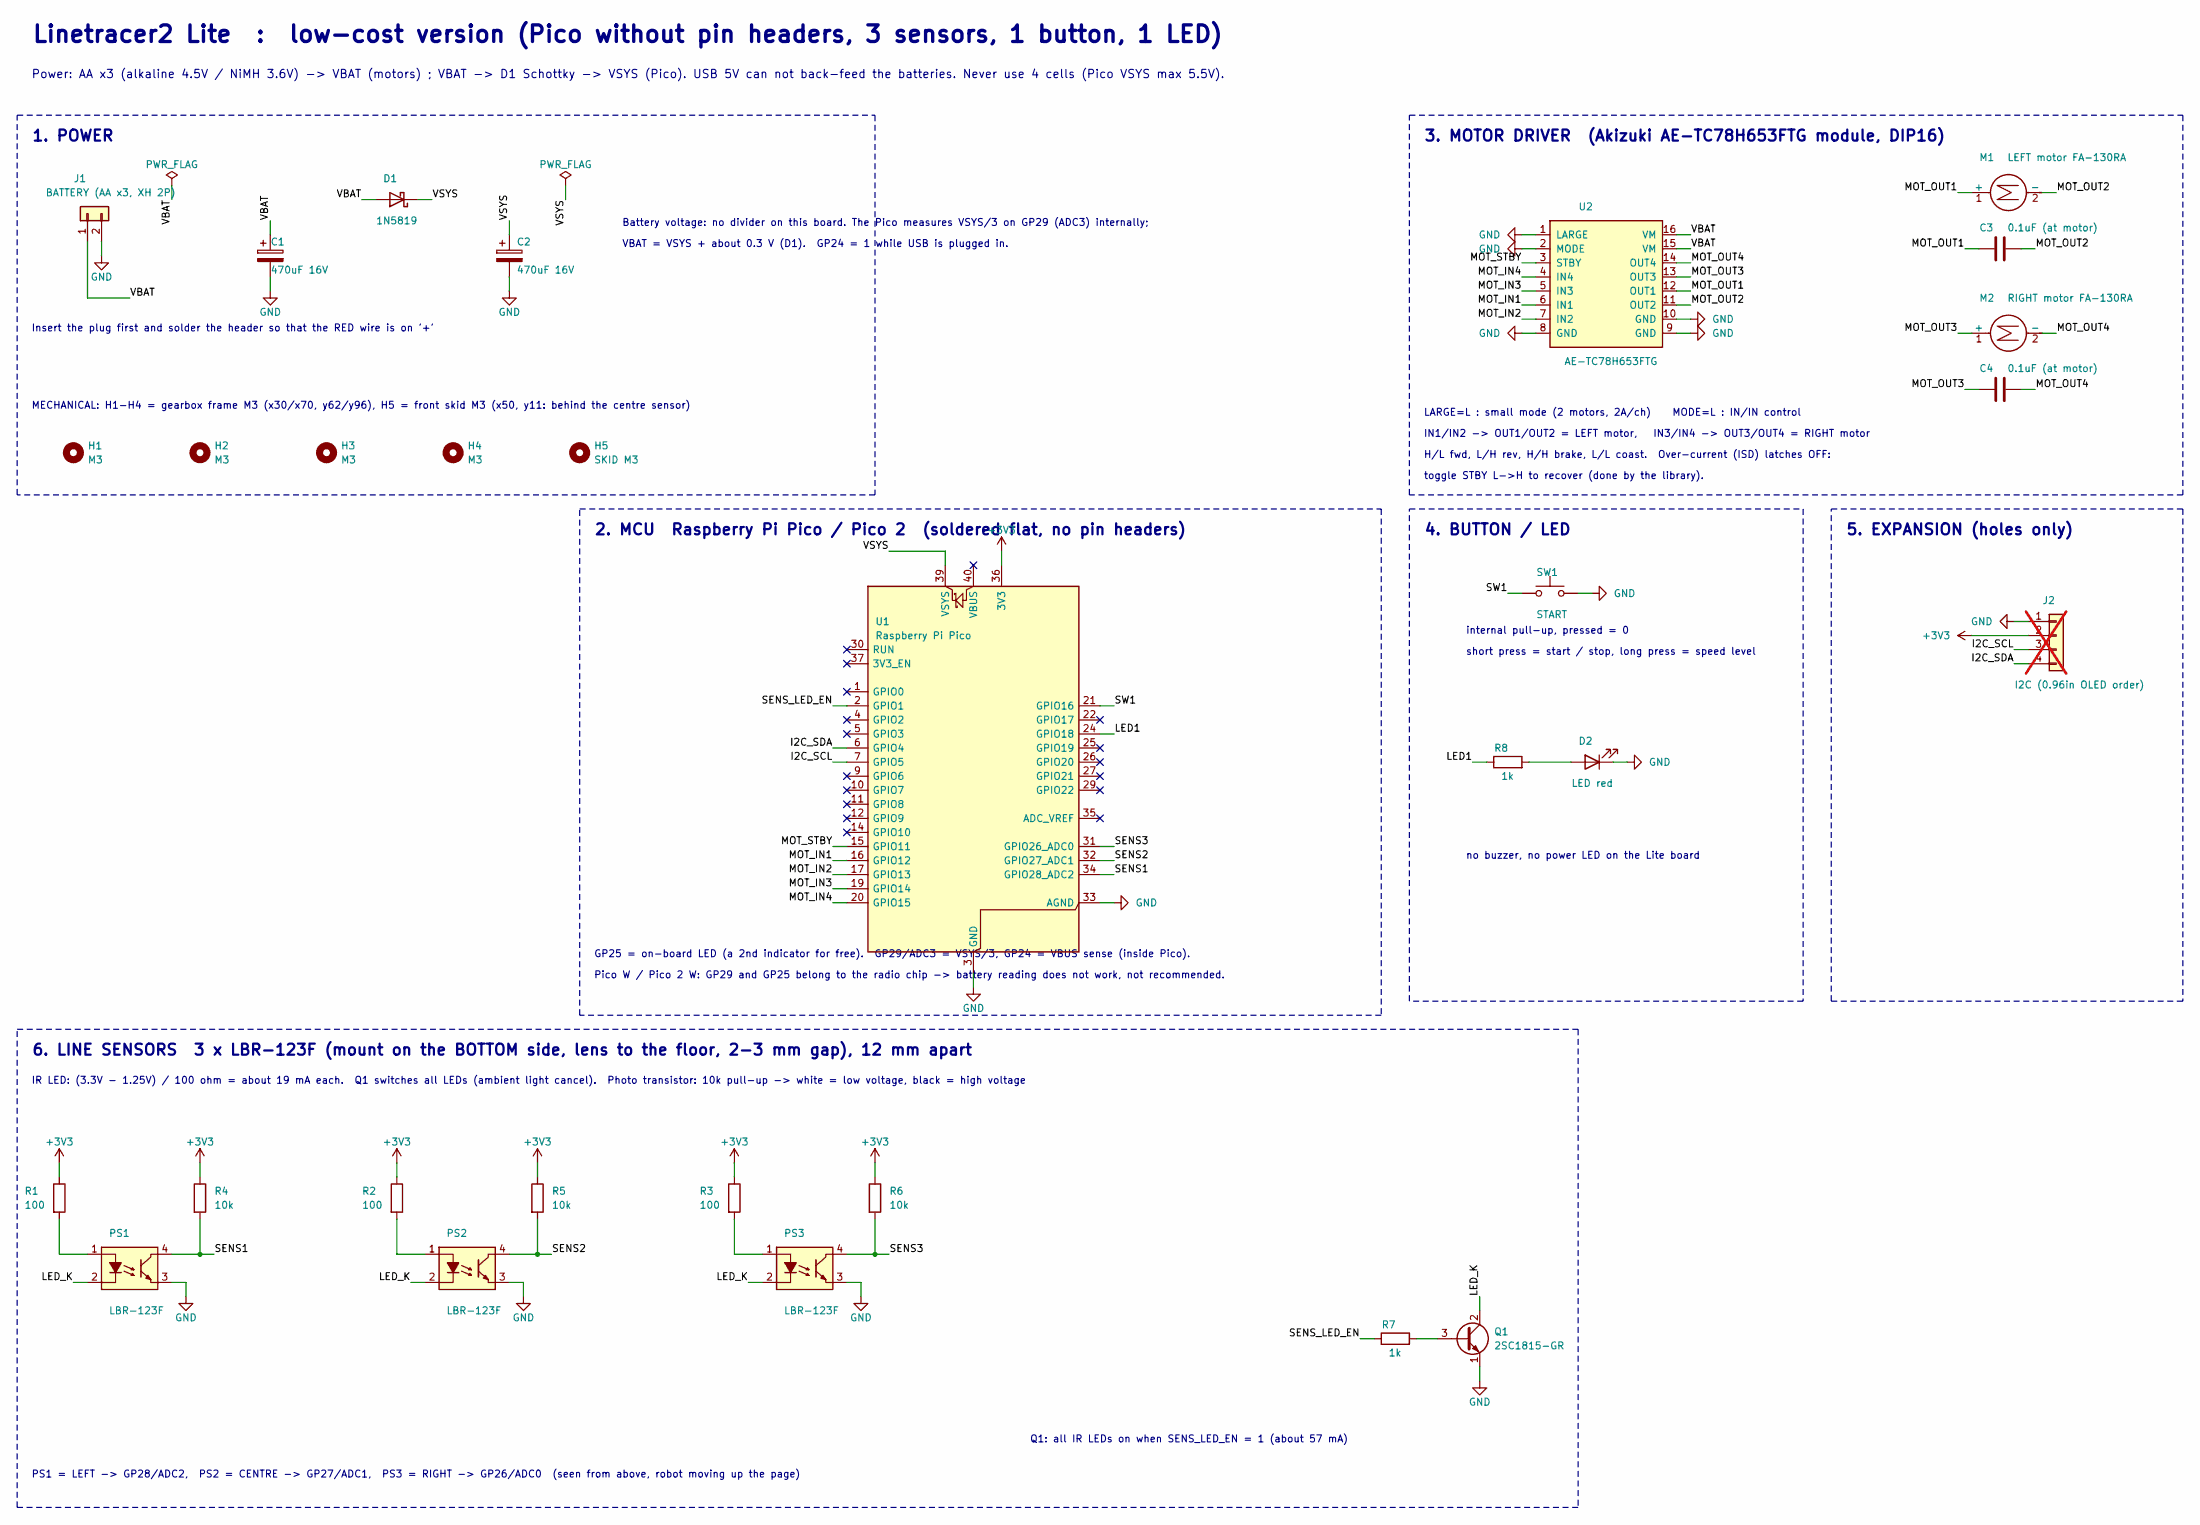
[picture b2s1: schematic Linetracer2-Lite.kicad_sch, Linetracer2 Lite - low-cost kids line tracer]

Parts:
C1, C2: 470uF 16V; CP_Radial_D8.0mm_P3.50mm
C3, C4: 0.1uF (at motor); C_Disc_D3.0mm_W2.0mm_P2.50mm
D1: 1N5819; D_DO-41_SOD81_P10.16mm_Horizontal
D2: LED red; LED_D3.0mm
H1, H2, H3, H4: M3; MountingHole_3.2mm_M3
H5: SKID M3; MountingHole_3.2mm_M3
J1: BATTERY (AA x3, XH 2P); BatteryXH_2P
J2: I2C (0.96in OLED order); PinHeader_1x04_P2.54mm_Vertical; not fitted
M1: LEFT motor FA-130RA; MotorPads_2P_Relief
M2: RIGHT motor FA-130RA; MotorPads_2P_Relief
PS1, PS2, PS3: LBR-123F
Q1: 2SC1815-GR; TO-92_Inline_Wide
R1, R2, R3: 100; R_Axial_DIN0207_L6.3mm_D2.5mm_P10.16mm_Horizontal
R4, R5, R6: 10k; R_Axial_DIN0207_L6.3mm_D2.5mm_P10.16mm_Horizontal
R7, R8: 1k; R_Axial_DIN0207_L6.3mm_D2.5mm_P10.16mm_Horizontal
SW1: START; SW_PUSH_6mm
U1: Raspberry Pi Pico; RaspberryPi_Pico_DirectSolder
U2: AE-TC78H653FTG

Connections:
+3V3: J2.2, R1.1, R2.1, R3.1, R4.1, R5.1, R6.1, U1.36 (3V3)
/I2C_SCL: J2.3, U1.7 (GPIO5)
/I2C_SDA: J2.4, U1.6 (GPIO4)
/LED1: R8.1, U1.24 (GPIO18)
/LED_K: PS1.2 (K), PS2.2 (K), PS3.2 (K), Q1.2 (C)
/MOT_IN1: U1.16 (GPIO12), U2.6 (IN1)
/MOT_IN2: U1.17 (GPIO13), U2.7 (IN2)
/MOT_IN3: U1.19 (GPIO14), U2.5 (IN3)
/MOT_IN4: U1.20 (GPIO15), U2.4 (IN4)
/MOT_OUT1: C3.1, M1.1 (+), U2.12 (OUT1)
/MOT_OUT2: C3.2, M1.2 (-), U2.11 (OUT2)
/MOT_OUT3: C4.1, M2.1 (+), U2.13 (OUT3)
/MOT_OUT4: C4.2, M2.2 (-), U2.14 (OUT4)
/MOT_STBY: U1.15 (GPIO11), U2.3 (STBY)
/SENS1: PS1.4 (C), R4.2, U1.34 (GPIO28_ADC2)
/SENS2: PS2.4 (C), R5.2, U1.32 (GPIO27_ADC1)
/SENS3: PS3.4 (C), R6.2, U1.31 (GPIO26_ADC0)
/SENS_LED_EN: R7.1, U1.2 (GPIO1)
/SW1: SW1.1, U1.21 (GPIO16)
/VBAT: C1.1, D1.2 (A), J1.1, U2.15 (VM), U2.16 (VM)
/VSYS: C2.1, D1.1 (K), U1.39 (VSYS)
GND: C1.2, C2.2, D2.1 (K), J1.2, J2.1, PS1.3 (E), PS2.3 (E), PS3.3 (E), Q1.1 (E), SW1.2, U1.3 (GND), U1.8 (GND), U1.13 (GND), U1.18 (GND), U1.23 (GND), U1.28 (GND), U1.33 (AGND), U1.38 (GND), U2.1 (LARGE), U2.2 (MODE), U2.8 (GND), U2.9 (GND), U2.10 (GND)
unnamed: D2.2 (A), R8.2
unnamed: PS1.1 (A), R1.2
unnamed: PS2.1 (A), R2.2
unnamed: PS3.1 (A), R3.2
unnamed: Q1.3 (B), R7.2

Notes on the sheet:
IN1/IN2 -> OUT1/OUT2 = LEFT motor, IN3/IN4 -> OUT3/OUT4 = RIGHT motor
Power: AA x3 (alkaline 4.5V / NiMH 3.6V) -> VBAT (motors) ; VBAT -> D1 Schottky -> VSYS (Pico). USB 5V can not back-feed the batteries. Never use 4 cells (Pico VSYS max 5.5V).
LARGE=L : small mode (2 motors, 2A/ch) MODE=L : IN/IN control
2. MCU Raspberry Pi Pico / Pico 2 (soldered flat, no pin headers)
Insert the plug first and solder the header so that the RED wire is on '+'
6. LINE SENSORS 3 x LBR-123F (mount on the BOTTOM side, lens to the floor, 2-3 mm gap), 12 mm apart
no buzzer, no power LED on the Lite board
Pico W / Pico 2 W: GP29 and GP25 belong to the radio chip -> battery reading does not work, not recommended.
1. POWER
MECHANICAL: H1-H4 = gearbox frame M3 (x30/x70, y62/y96), H5 = front skid M3 (x50, y11: behind the centre sensor)
5. EXPANSION (holes only)
Q1: all IR LEDs on when SENS_LED_EN = 1 (about 57 mA)
PS1 = LEFT -> GP28/ADC2, PS2 = CENTRE -> GP27/ADC1, PS3 = RIGHT -> GP26/ADC0 (seen from above, robot moving up the page)
Battery voltage: no divider on this board. The Pico measures VSYS/3 on GP29 (ADC3) internally;
4. BUTTON / LED
VBAT = VSYS + about 0.3 V (D1). GP24 = 1 while USB is plugged in.
GP25 = on-board LED (a 2nd indicator for free). GP29/ADC3 = VSYS/3, GP24 = VBUS sense (inside Pico).
H/L fwd, L/H rev, H/H brake, L/L coast. Over-current (ISD) latches OFF:
3. MOTOR DRIVER (Akizuki AE-TC78H653FTG module, DIP16)
IR LED: (3.3V - 1.25V) / 100 ohm = about 19 mA each. Q1 switches all LEDs (ambient light cancel). Photo transistor: 10k pull-up -> white = low voltage, black = high voltage
short press = start / stop, long press = speed level
Linetracer2 Lite : low-cost version (Pico without pin headers, 3 sensors, 1 button, 1 LED)
internal pull-up, pressed = 0
toggle STBY L->H to recover (done by the library).
